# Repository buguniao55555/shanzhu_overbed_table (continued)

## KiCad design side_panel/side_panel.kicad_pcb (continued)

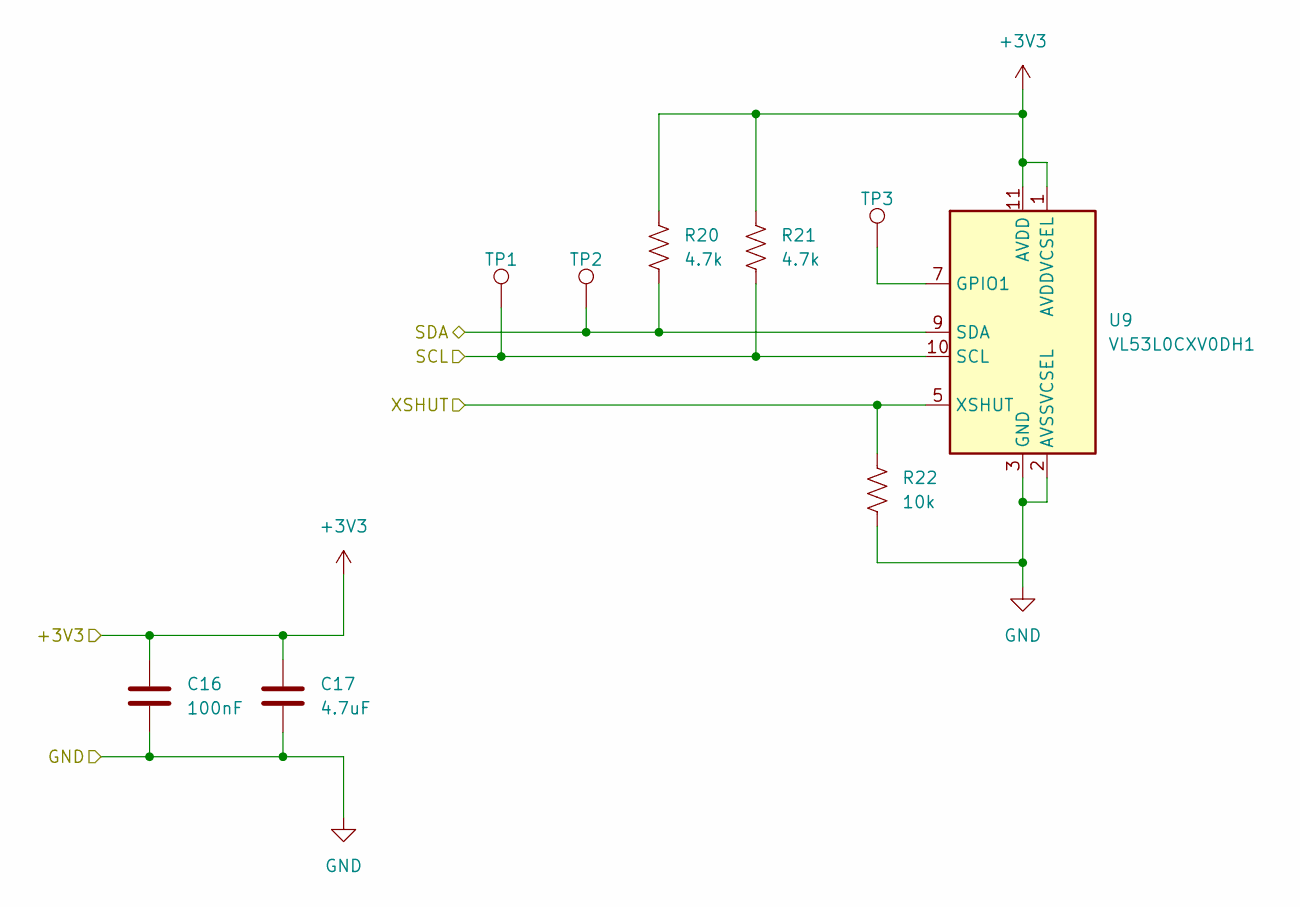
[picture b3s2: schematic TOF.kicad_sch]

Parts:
C16: 100nF; C_0603_1608Metric
C17: 4.7uF; C_0603_1608Metric
R20, R21: 4.7k; R_0603_1608Metric
R22: 10k; R_0603_1608Metric
TP1, TP2, TP3: 1.0mm; TestPoint-1.0mm
U9: VL53L0CXV0DH1; ST_VL53L0X

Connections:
+3V3: C16.1, C17.1, R20.1, R21.1, U9.1 (AVDDVCSEL), U9.11 (AVDD); also elsewhere on the board
/SCL: R21.2, TP1.1 (1_1), U9.10 (SCL); also elsewhere on the board
/SDA: R20.2, TP2.1 (1_1), U9.9 (SDA); also elsewhere on the board
/TOF_XSHUT: R22.1, U9.5 (XSHUT); also elsewhere on the board
GND: C16.2, C17.2, R22.2, U9.2 (AVSSVCSEL), U9.3 (GND), U9.4 (GND), U9.6 (GND), U9.12 (GND); also elsewhere on the board
unnamed: TP3.1 (1_1), U9.7 (GPIO1)

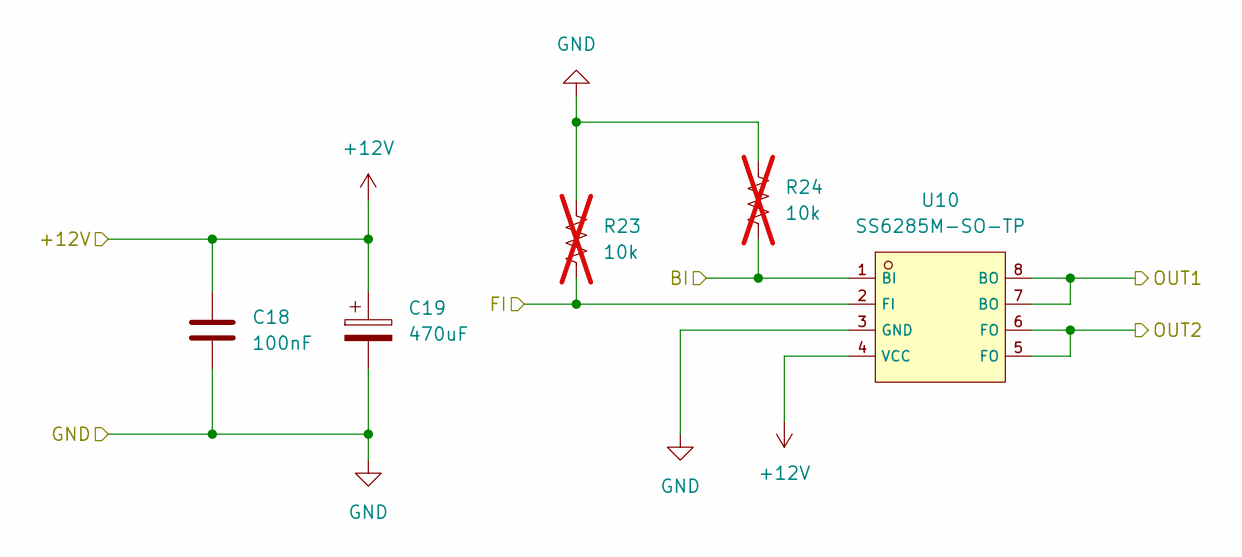
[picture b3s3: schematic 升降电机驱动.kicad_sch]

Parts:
C18: 100nF; C_0603_1608Metric
C19: 470uF; CP_Elec_10x10.5
R23, R24: 10k; R_0603_1608Metric; not fitted
U10: SS6285M-SO-TP; C5370898_SOIC-8_L4_9-W3_9-P1_27-LS6_0-BL; LCSC C5370898

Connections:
+12V: C18.1, C19.1, U10.4 (VCC); also elsewhere on the board
/MOTOR_BI: R24.2, U10.1 (BI); also elsewhere on the board
/MOTOR_FI: R23.2, U10.2 (FI); also elsewhere on the board
/MOTOR_OUT1: U10.5 (FO), U10.6 (FO); also elsewhere on the board
/MOTOR_OUT2: U10.7 (BO), U10.8 (BO); also elsewhere on the board
GND: C18.2, C19.2, R23.1, R24.1, U10.3 (GND); also elsewhere on the board

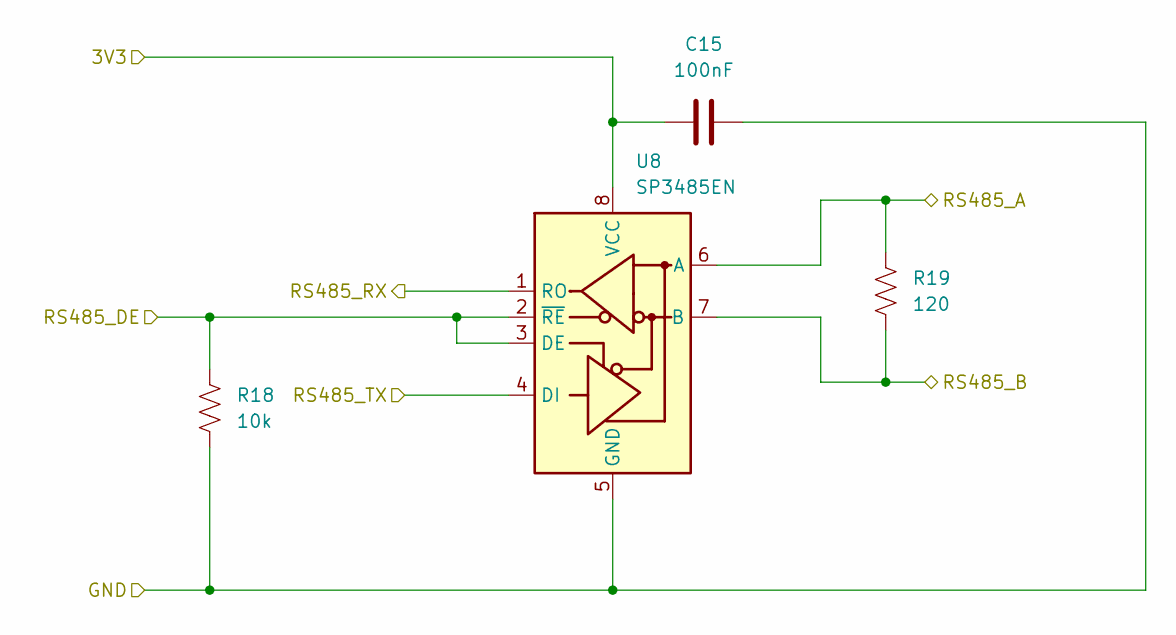
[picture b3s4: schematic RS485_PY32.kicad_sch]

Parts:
C15: 100nF; C_0603_1608Metric
R18: 10k; R_0603_1608Metric
R19: 120; R_0603_1608Metric
U8: SP3485EN; SOIC-8_3.9x4.9mm_P1.27mm

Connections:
+3V3: C15.1, U8.8 (VCC); also elsewhere on the board
/RS485_A: R19.1, U8.6 (A); also elsewhere on the board
/RS485_B: R19.2, U8.7 (B); also elsewhere on the board
/RS485_PY32/RS485_DE: R18.1, U8.2 (~RE), U8.3 (DE); also elsewhere on the board
/RS485_PY32/RS485_RX: U8.1 (RO); also elsewhere on the board
/RS485_PY32/RS485_TX: U8.4 (DI); also elsewhere on the board
GND: C15.2, R18.2, U8.5 (GND); also elsewhere on the board

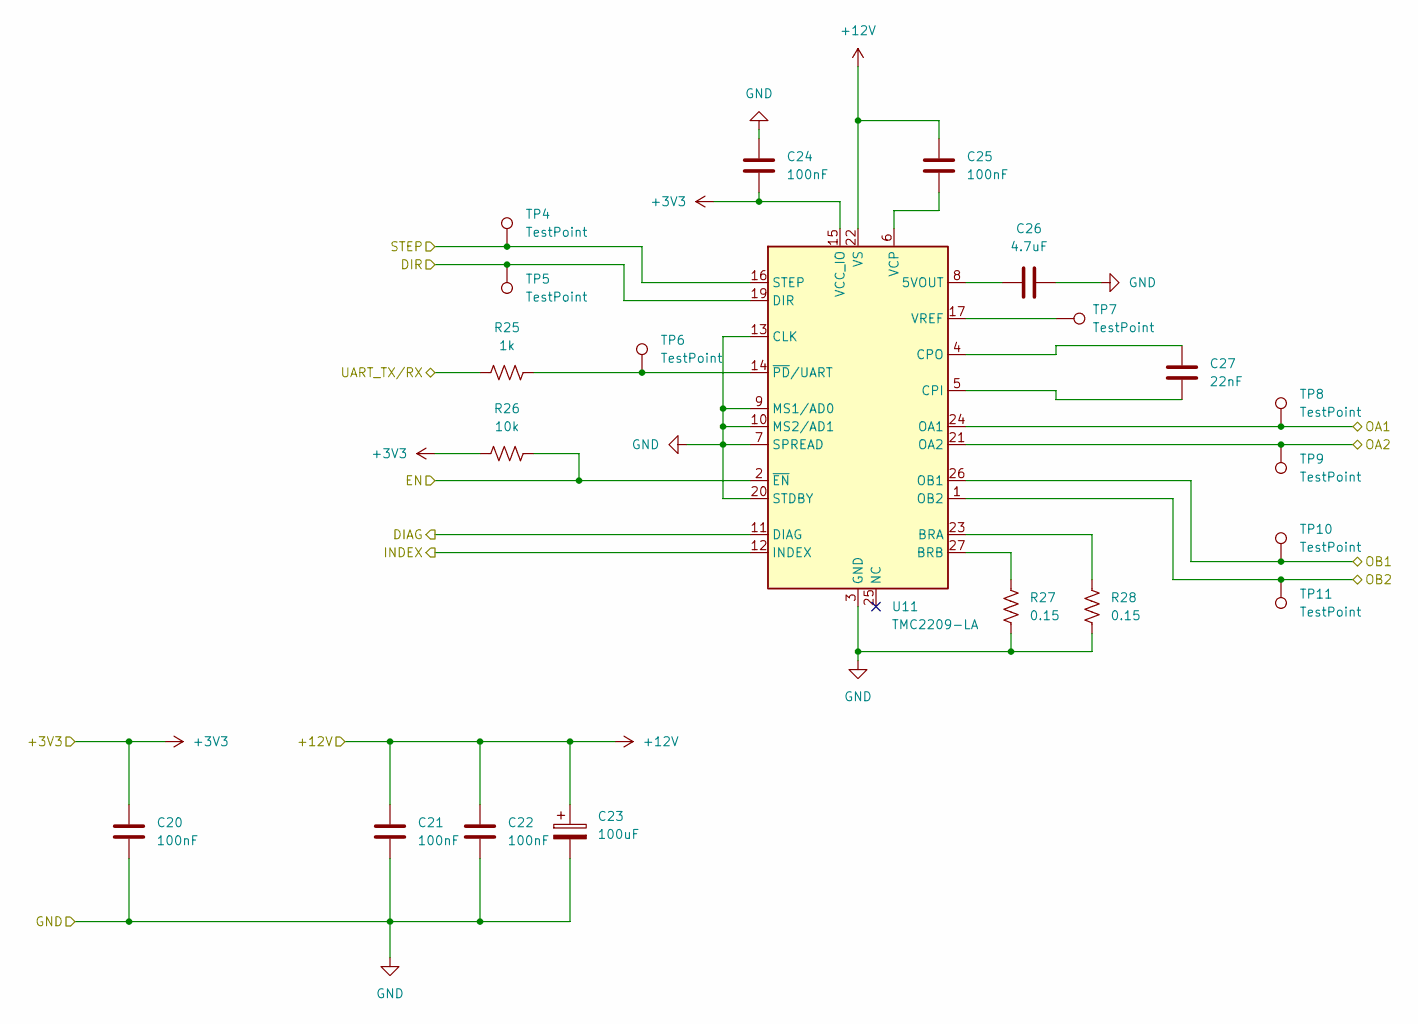
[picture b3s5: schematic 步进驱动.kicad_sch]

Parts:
C20, C21, C22, C24, C25: 100nF; C_0603_1608Metric
C23: 100uF; CP_Elec_6.3x7.7
C26: 4.7uF; C_0603_1608Metric
C27: 22nF; C_0603_1608Metric
R25: 1k; R_0603_1608Metric
R26: 10k; R_0603_1608Metric
R27, R28: 0.15; R_0603_1608Metric
TP4, TP5, TP6, TP7, TP8, TP9, TP10, TP11: TestPoint; TestPoint-1.0mm
U11: TMC2209-LA; VQFN-28-1EP_5x5mm_P0.5mm_EP3.7x3.7mm_ThermalVias

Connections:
+3V3: C20.1, C24.1, R26.2, U11.15 (VCC_IO); also elsewhere on the board
+12V: C21.1, C22.1, C23.1, C25.2, U11.22 (VS), U11.28 (VS); also elsewhere on the board
/STEPPER_OA1: TP8.1 (1_1), U11.24 (OA1); also elsewhere on the board
/STEPPER_OA2: TP9.1 (1_1), U11.21 (OA2); also elsewhere on the board
/STEPPER_OB1: TP10.1 (1_1), U11.26 (OB1); also elsewhere on the board
/STEPPER_OB2: TP11.1 (1_1), U11.1 (OB2); also elsewhere on the board
/TMC_DIAG: U11.11 (DIAG); also elsewhere on the board
/TMC_DIR: TP5.1 (1_1), U11.19 (DIR); also elsewhere on the board
/TMC_EN: R26.1, U11.2 (~EN); also elsewhere on the board
/TMC_STEP: TP4.1 (1_1), U11.16 (STEP); also elsewhere on the board
/TMC_UART: R25.2; also elsewhere on the board
/步进驱动/INDEX: U11.12 (INDEX)
GND: C20.2, C21.2, C22.2, C23.2, C24.2, C26.2, R27.2, R28.2, U11.3 (GND), U11.7 (SPREAD), U11.9 (MS1/AD0), U11.10 (MS2/AD1), U11.13 (CLK), U11.18 (GND), U11.20 (STDBY), U11.29 (GND); also elsewhere on the board
unnamed: C26.1, U11.8 (5VOUT)
unnamed: R28.1, U11.23 (BRA)
unnamed: R27.1, U11.27 (BRB)
unnamed: C27.1, U11.5 (CPI)
unnamed: C27.2, U11.4 (CPO)
unnamed: C25.1, U11.6 (VCP)
unnamed: TP7.1 (1_1), U11.17 (VREF)
unnamed: R25.1, TP6.1 (1_1), U11.14 (~PD/UART)

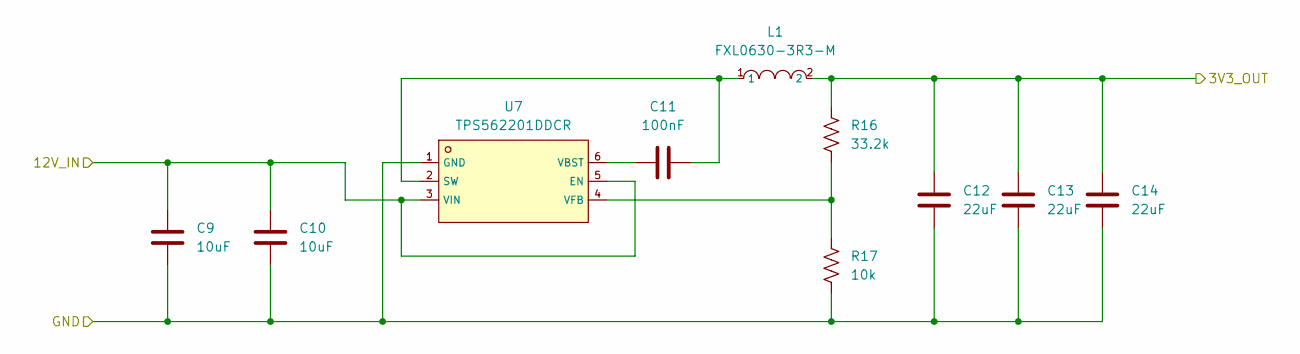
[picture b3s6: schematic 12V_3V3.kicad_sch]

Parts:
C9, C10: 10uF; C_0805_2012Metric
C11: 100nF; C_0805_2012Metric
C12, C13, C14: 22uF; C_0805_2012Metric
L1: FXL0630-3R3-M; C167219_IND-SMD_L7_0-W6_6; LCSC C167219
R16: 33.2k; R_0603_1608Metric
R17: 10k; R_0603_1608Metric
U7: TPS562201DDCR; C90061_SOT-23-6_L2_9-W1_6-P0_95-LS2_8-BR; LCSC C90061

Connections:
+3V3: C12.1, C13.1, C14.1, L1.2, R16.2; also elsewhere on the board
+12V: C9.1, C10.1, U7.3 (VIN), U7.5 (EN); also elsewhere on the board
GND: C9.2, C10.2, C12.2, C13.2, C14.2, R17.1, U7.1 (GND); also elsewhere on the board
unnamed: C11.2, L1.1, U7.2 (SW)
unnamed: C11.1, U7.6 (VBST)
unnamed: R16.1, R17.2, U7.4 (VFB)

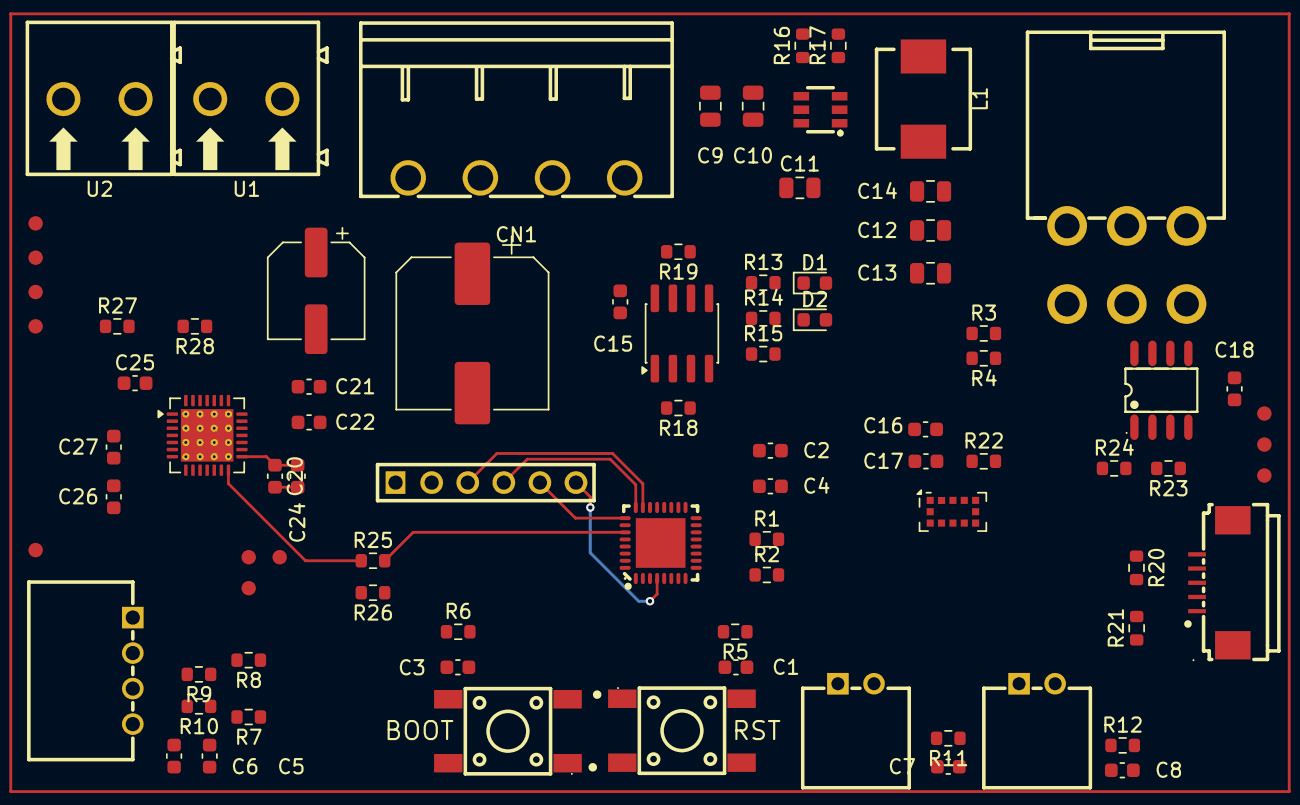
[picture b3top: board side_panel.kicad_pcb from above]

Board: 2 copper layers, 86 parts (0 on the bottom side), 55 nets.
